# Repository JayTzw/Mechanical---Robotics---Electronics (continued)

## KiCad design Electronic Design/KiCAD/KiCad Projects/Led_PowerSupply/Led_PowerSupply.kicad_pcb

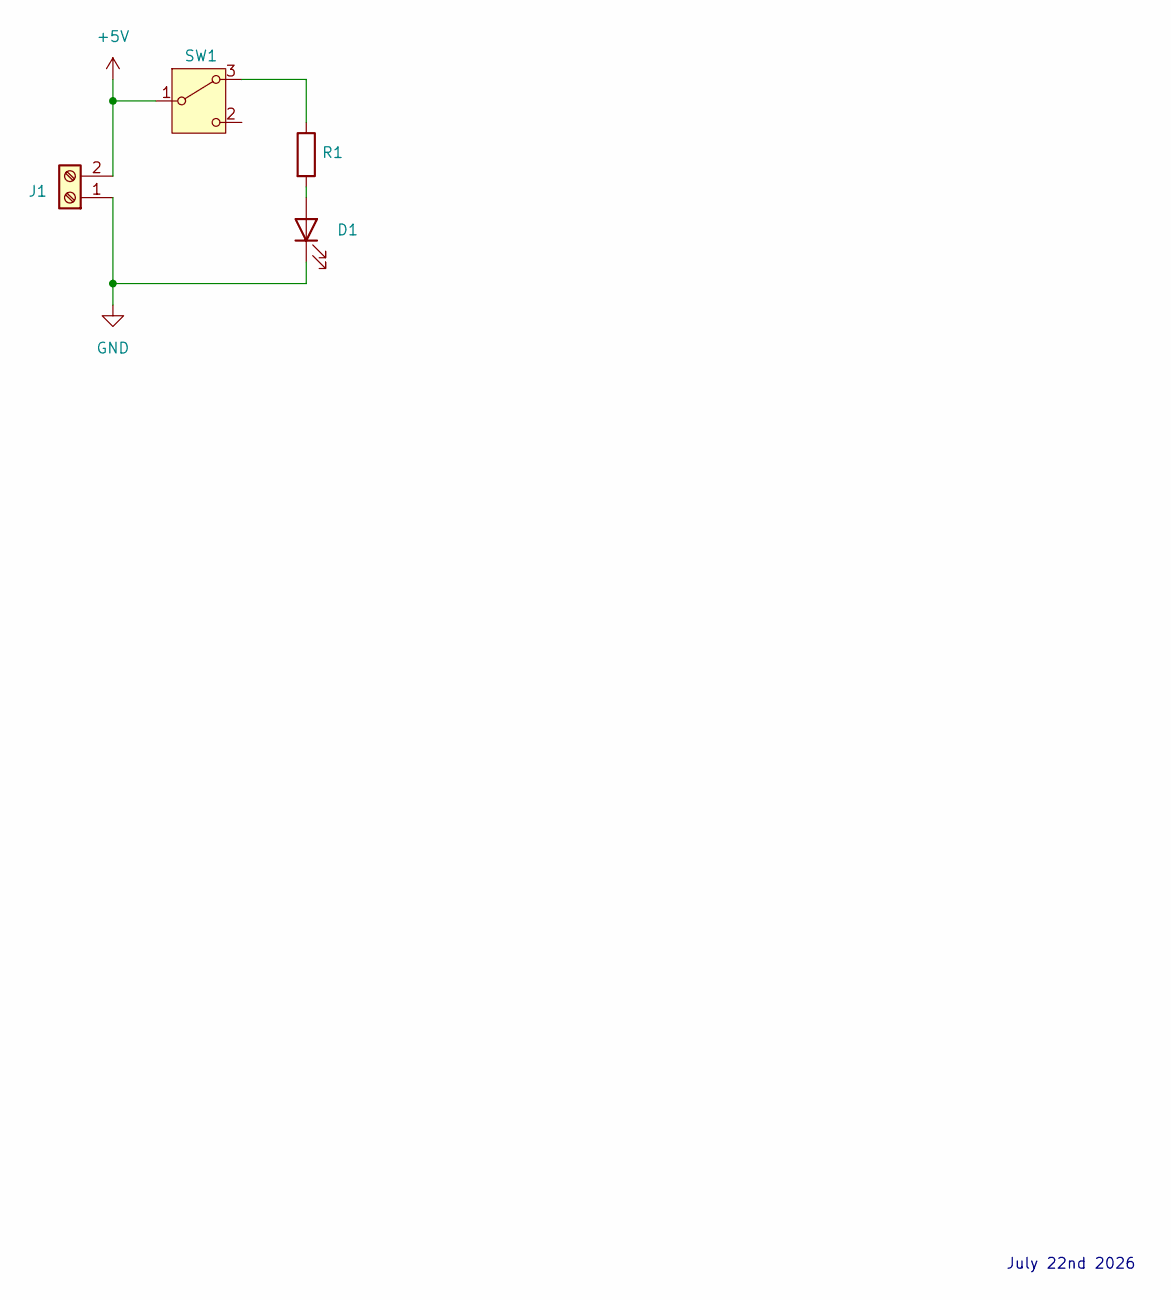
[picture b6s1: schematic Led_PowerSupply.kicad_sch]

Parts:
D1: LED
J1: Screw_Terminal_01x02
R1: R
SW1: SW_SPDT_312

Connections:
+5V: J1.2, SW1.1 (B)
GND: D1.1 (K), J1.1
unnamed: D1.2 (A), R1.2
unnamed: R1.1, SW1.3 (A)

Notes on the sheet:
July 22nd 2026

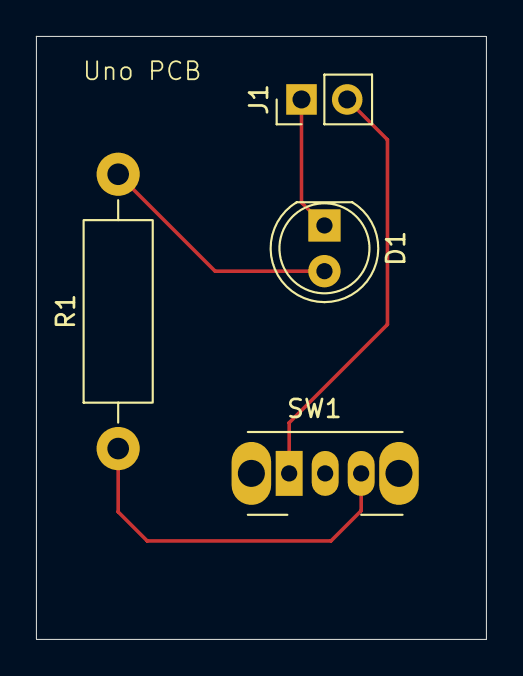
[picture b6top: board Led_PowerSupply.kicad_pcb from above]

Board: 2 copper layers, 25.0 x 33.5 mm, 4 parts (0 on the bottom side), 4 nets.
